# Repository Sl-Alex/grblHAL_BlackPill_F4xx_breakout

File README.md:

# What is it
It's a breakout board for F411 board (black pill) running [grblHAL FW][grblhal_fw]. It is compatible with the default black pill mapping.

## What is tested and confirmed to work

Limits, step/dir outputs and probing are tested and work fine.

> Limits and probing inputs (especially probing) enable a very convenient tool change procedure, when the only thing you have to do is to change the tool and click "cycle start".

Buttons, step enable and spindle enable also work, spindle PWM and auxiliary inputs/outputs are not tested. 

## Pinout

![Pinout][pinout]

The left part of the board is fully isolated from the right part, provided that two isolated power supplies are used.

There is no isolation between the MCU board and the outputs, but this is not a problem taking into account that all these outputs go either to optocouplers or relays.

```NCI``` stands for **N**on-**C**onnected **I**nput, ```NCO``` is an output.

## Remarks

All outputs provide 12V, so be careful connecting step motor drivers without any current limiting circuit.
Some drivers have just one resistor in series with the optocoupler LED, others have a bit more complex constant current circuits, like this:

![Constant current][constant_current]

Most of the drivers without the constant current circuit expect 5V input, so adding a resistor in series with the driver input would be a good solution.
As an alternative, 5V power supply could be used for the output part.

[grblhal_fw]: https://github.com/grblHAL
[pinout]: images/Pinout.png
[constant_current]: images/ConstantCurrent.png

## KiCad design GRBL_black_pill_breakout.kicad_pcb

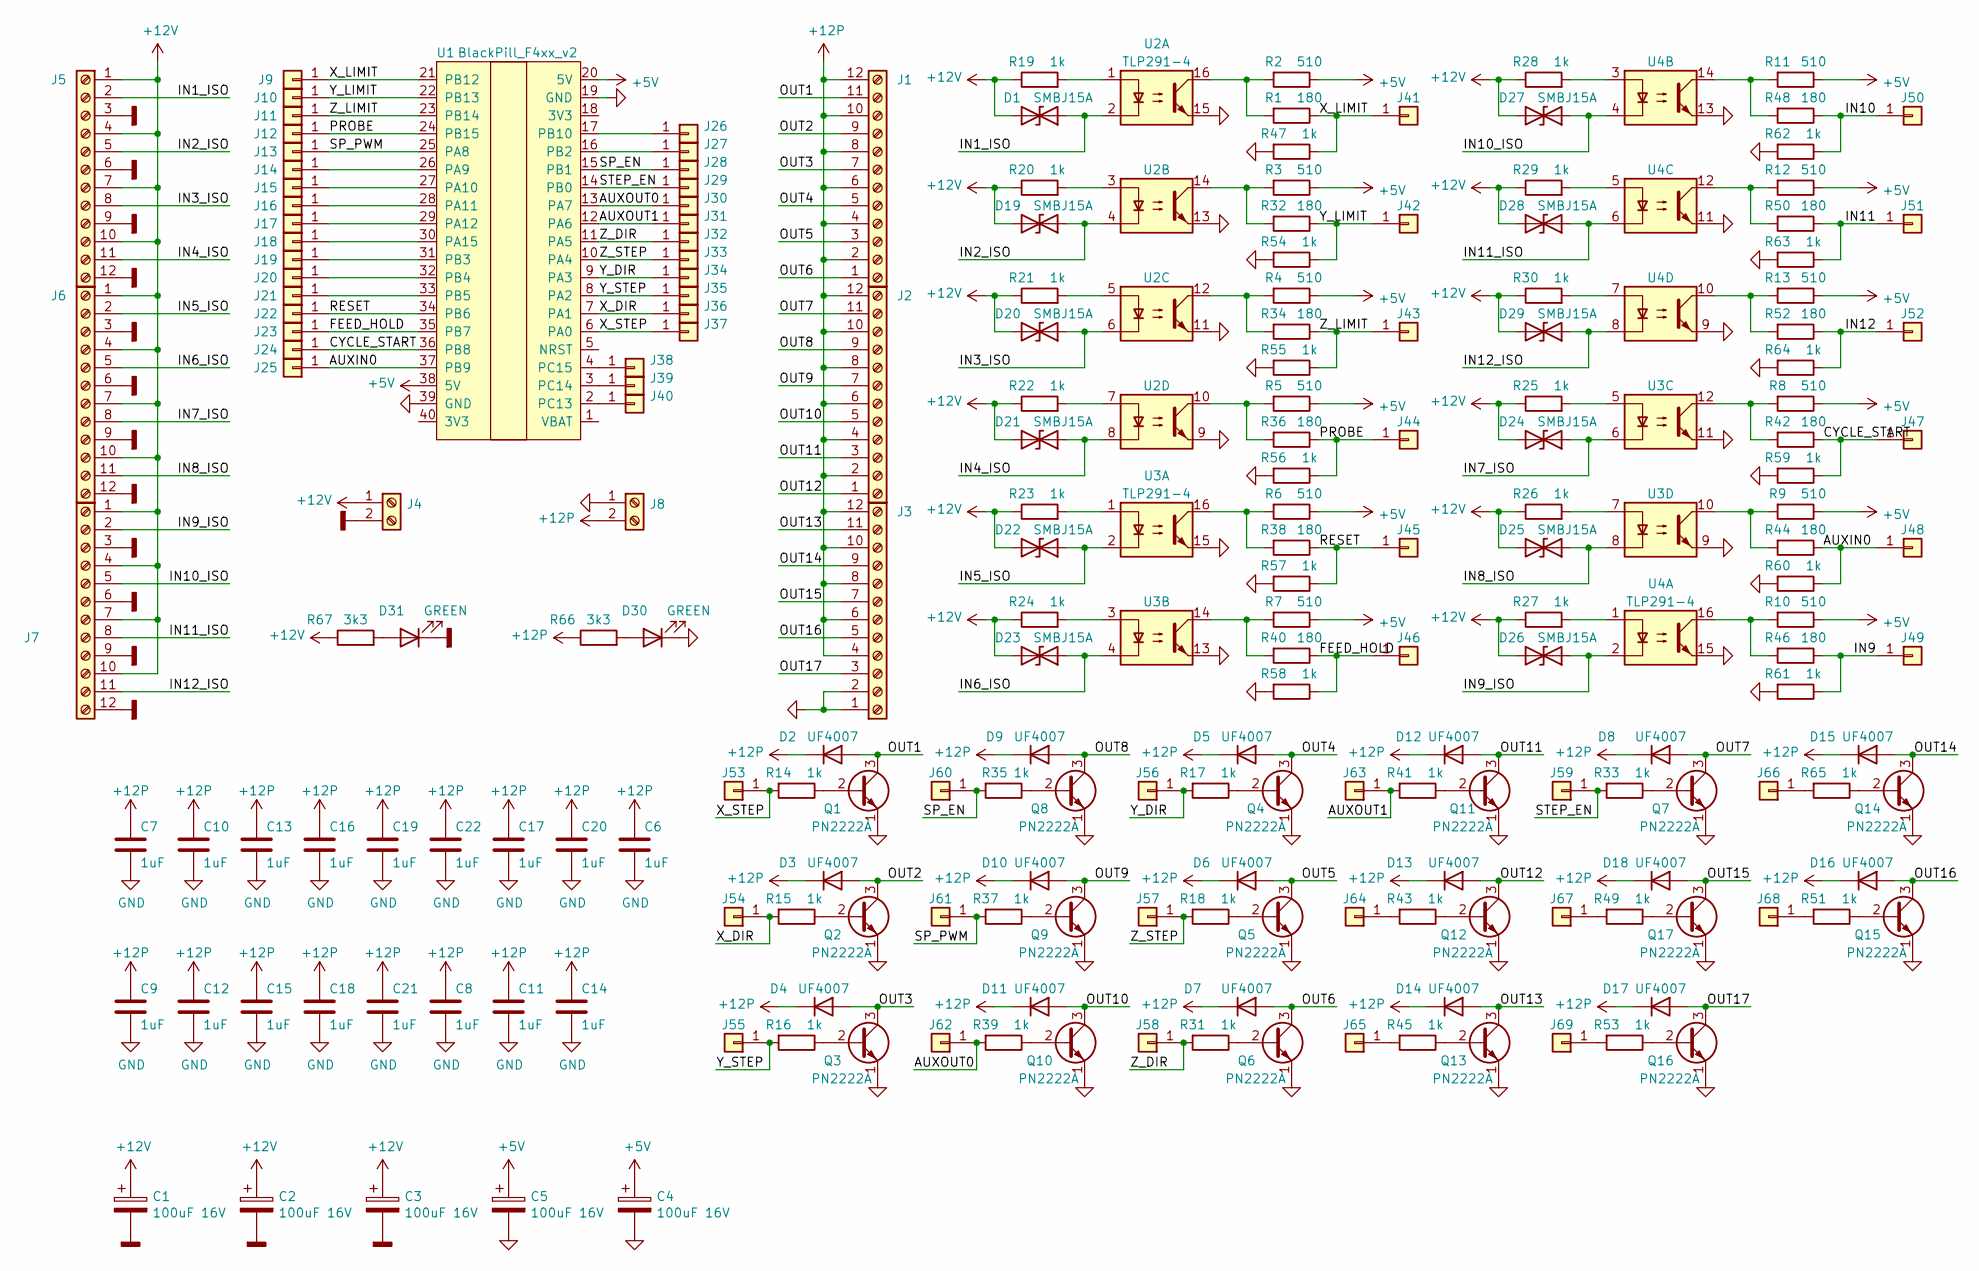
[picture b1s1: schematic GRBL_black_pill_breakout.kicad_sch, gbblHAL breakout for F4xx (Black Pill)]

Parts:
C1, C2, C3, C4, C5: 100uF 16V; CP_Radial_D5.0mm_P2.50mm
C6, C7, C8, C9, C10, C11, C12, C13, C14, C15, C16, C17, C18, C19, C20, C21, C22: 1uF; C_0603_1608Metric
D1, D19, D20, D21, D22, D23, D24, D25, D26, D27, D28, D29: SMBJ15A; D_SMB
D2, D3, D4, D5, D6, D7, D8, D9, D10, D11, D12, D13, D14, D15, D16, D17, D18: UF4007; D_DO-41_SOD81_P2.54mm_Vertical_KathodeUp
D30, D31: GREEN; LED_D3.0mm
J1, J2, J3, J5, J6, J7: Screw_Terminal_01x12; TerminalBlock_Phoenix_MPT-0,5-12-2.54_1x12_P2.54mm_Horizont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
J4, J8: Screw_Terminal_01x02; TerminalBlock_Phoenix_MKDS-1,5-2-5.08_1x02_P5.08mm_Horizont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
J9, J10, J11, J12, J13, J14, J15, J16, J17, J18, J19, J20, J21, J22, J23, J24, J25, J26, J27, J28, J29, J30, J31, J32, J33, J34, J35, J36, J37, J38, J39, J40, J41, J42, J43, J44, J45, J46, J47, J48, J49, J50, J51, J52, J53, J54, J55, J56, J57, J58, J59, J60, J61, J62, J63, J64, J65, J66, J67, J68, J69: Conn_01x01; PinHeader_1x01_P2.54mm_Vertical
Q1, Q2, Q3, Q4, Q5, Q6, Q7, Q8, Q9, Q10, Q11, Q12, Q13, Q14, Q15, Q16, Q17: PN2222A; TO-92_Inline
R1, R32, R34, R36, R38, R40, R42, R44, R46, R48, R50, R52: 180; R_0603_1608Metric
R2, R3, R4, R5, R6, R7, R8, R9, R10, R11, R12, R13: 510; R_0603_1608Metric
R14, R15, R16, R17, R18, R31, R33, R35, R37, R39, R41, R43, R45, R47, R49, R51, R53, R54, R55, R56, R57, R58, R59, R60, R61, R62, R63, R64, R65: 1k; R_0603_1608Metric
R19, R20, R21, R22, R23, R24, R25, R26, R27, R28, R29, R30: 1k; R_Axial_DIN0207_L6.3mm_D2.5mm_P2.54mm_Vertical
R66, R67: 3k3; R_Axial_DIN0207_L6.3mm_D2.5mm_P2.54mm_Vertical
U1: BlackPill_F4xx_v2
U2, U3, U4: TLP291-4; SOP-16_4.4x10.4mm_P1.27mm

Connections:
+5V: C4.1, C5.1, R2.1, R3.1, R4.1, R5.1, R6.1, R7.1, R8.1, R9.1, R10.1, R11.1, R12.1, R13.1, U1.20 (5V), U1.38 (5V)
+12P: C6.1, C7.1, C8.1, C9.1, C10.1, C11.1, C12.1, C13.1, C14.1, C15.1, C16.1, C17.1, C18.1, C19.1, C20.1, C21.1, C22.1, D2.1 (K), D3.1 (K), D4.1 (K), D5.1 (K), D6.1 (K), D7.1 (K), D8.1 (K), D9.1 (K), D10.1 (K), D11.1 (K), D12.1 (K), D13.1 (K), D14.1 (K), D15.1 (K), D16.1 (K), D17.1 (K), D18.1 (K), J1.2, J1.4, J1.6, J1.8, J1.10, J1.12, J2.2, J2.4, J2.6, J2.8, J2.10, J2.12, J3.4, J3.6, J3.8, J3.10, J3.12, J8.2, R66.1
+12V: C1.1, C2.1, C3.1, D1.2 (A2), D19.2 (A2), D20.2 (A2), D21.2 (A2), D22.2 (A2), D23.2 (A2), D24.2 (A2), D25.2 (A2), D26.2 (A2), D27.2 (A2), D28.2 (A2), D29.2 (A2), J4.1, J5.1, J5.4, J5.7, J5.10, J6.1, J6.4, J6.7, J6.10, J7.1, J7.4, J7.7, J7.10, R19.1, R20.1, R21.1, R22.1, R23.1, R24.1, R25.1, R26.1, R27.1, R28.1, R29.1, R30.1, R67.1
/AUXIN0: J25.1, J48.1, R44.1, R60.1, U1.37 (PB9)
/AUXOUT0: J30.1, J62.1, R39.2, U1.13 (PA7)
/AUXOUT1: J31.1, J63.1, R41.2, U1.12 (PA6)
/CYCLE_START: J24.1, J47.1, R42.1, R59.1, U1.36 (PB8)
/FEED_HOLD: J23.1, J46.1, R40.1, R58.1, U1.35 (PB7)
/IN1_ISO: D1.1 (A1), J5.2, U2.2
/IN2_ISO: D19.1 (A1), J5.5, U2.4
/IN3_ISO: D20.1 (A1), J5.8, U2.6
/IN4_ISO: D21.1 (A1), J5.11, U2.8
/IN5_ISO: D22.1 (A1), J6.2, U3.2
/IN6_ISO: D23.1 (A1), J6.5, U3.4
/IN7_ISO: D24.1 (A1), J6.8, U3.6
/IN8_ISO: D25.1 (A1), J6.11, U3.8
/IN9: J49.1, R46.1, R61.1
/IN9_ISO: D26.1 (A1), J7.2, U4.2
/IN10: J50.1, R48.1, R62.1
/IN10_ISO: D27.1 (A1), J7.5, U4.4
/IN11: J51.1, R50.1, R63.1
/IN11_ISO: D28.1 (A1), J7.8, U4.6
/IN12: J52.1, R52.1, R64.1
/IN12_ISO: D29.1 (A1), J7.11, U4.8
/OUT1: D2.2 (A), J1.11, Q1.3 (C)
/OUT2: D3.2 (A), J1.9, Q2.3 (C)
/OUT3: D4.2 (A), J1.7, Q3.3 (C)
/OUT4: D5.2 (A), J1.5, Q4.3 (C)
/OUT5: D6.2 (A), J1.3, Q5.3 (C)
/OUT6: D7.2 (A), J1.1, Q6.3 (C)
/OUT7: D8.2 (A), J2.11, Q7.3 (C)
/OUT8: D9.2 (A), J2.9, Q8.3 (C)
/OUT9: D10.2 (A), J2.7, Q9.3 (C)
/OUT10: D11.2 (A), J2.5, Q10.3 (C)
/OUT11: D12.2 (A), J2.3, Q11.3 (C)
/OUT12: D13.2 (A), J2.1, Q12.3 (C)
/OUT13: D14.2 (A), J3.11, Q13.3 (C)
/OUT14: D15.2 (A), J3.9, Q14.3 (C)
/OUT15: D18.2 (A), J3.7, Q17.3 (C)
/OUT16: D16.2 (A), J3.5, Q15.3 (C)
/OUT17: D17.2 (A), J3.3, Q16.3 (C)
/PROBE: J12.1, J44.1, R36.1, R56.1, U1.24 (PB15)
/RESET: J22.1, J45.1, R38.1, R57.1, U1.34 (PB6)
/SP_EN: J28.1, J60.1, R35.2, U1.15 (PB1)
/SP_PWM: J13.1, J61.1, R37.2, U1.25 (PA8)
/STEP_EN: J29.1, J59.1, R33.2, U1.14 (PB0)
/X_DIR: J36.1, J54.1, R15.2, U1.7 (PA1)
/X_LIMIT: J9.1, J41.1, R1.1, R47.1, U1.21 (PB12)
/X_STEP: J37.1, J53.1, R14.2, U1.6 (PA0)
/Y_DIR: J34.1, J56.1, R17.2, U1.9 (PA3)
/Y_LIMIT: J10.1, J42.1, R32.1, R54.1, U1.22 (PB13)
/Y_STEP: J35.1, J55.1, R16.2, U1.8 (PA2)
/Z_DIR: J32.1, J58.1, R31.2, U1.11 (PA5)
/Z_LIMIT: J11.1, J43.1, R34.1, R55.1, U1.23 (PB14)
/Z_STEP: J33.1, J57.1, R18.2, U1.10 (PA4)
GND: C4.2, C5.2, C6.2, C7.2, C8.2, C9.2, C10.2, C11.2, C12.2, C13.2, C14.2, C15.2, C16.2, C17.2, C18.2, C19.2, C20.2, C21.2, C22.2, D30.1 (K), J3.1, J3.2, J8.1, Q1.1 (E), Q2.1 (E), Q3.1 (E), Q4.1 (E), Q5.1 (E), Q6.1 (E), Q7.1 (E), Q8.1 (E), Q9.1 (E), Q10.1 (E), Q11.1 (E), Q12.1 (E), Q13.1 (E), Q14.1 (E), Q15.1 (E), Q16.1 (E), Q17.1 (E), R47.2, R54.2, R55.2, R56.2, R57.2, R58.2, R59.2, R60.2, R61.2, R62.2, R63.2, R64.2, U1.19 (GND), U1.39 (GND), U2.9, U2.11, U2.13, U2.15, U3.9, U3.11, U3.13, U3.15, U4.9, U4.11, U4.13, U4.15
GNDD: C1.2, C2.2, C3.2, D31.1 (K), J4.2, J5.3, J5.6, J5.9, J5.12, J6.3, J6.6, J6.9, J6.12, J7.3, J7.6, J7.9, J7.12
unnamed: D30.2 (A), R66.2
unnamed: D31.2 (A), R67.2
unnamed: J14.1, U1.26 (PA9)
unnamed: J15.1, U1.27 (PA10)
unnamed: J16.1, U1.28 (PA11)
unnamed: J17.1, U1.29 (PA12)
unnamed: J18.1, U1.30 (PA15)
unnamed: J19.1, U1.31 (PB3)
unnamed: J20.1, U1.32 (PB4)
unnamed: J21.1, U1.33 (PB5)
unnamed: J26.1, U1.17 (PB10)
unnamed: J27.1, U1.16 (PB2)
unnamed: J38.1, U1.4 (PC15)
unnamed: J39.1, U1.3 (PC14)
unnamed: J40.1, U1.2 (PC13)
unnamed: J64.1, R43.2
unnamed: J65.1, R45.2
unnamed: J66.1, R65.2
unnamed: J67.1, R49.2
unnamed: J68.1, R51.2
unnamed: J69.1, R53.2
unnamed: Q1.2 (B), R14.1
unnamed: Q2.2 (B), R15.1
unnamed: Q3.2 (B), R16.1
unnamed: Q4.2 (B), R17.1
unnamed: Q5.2 (B), R18.1
unnamed: Q6.2 (B), R31.1
unnamed: Q7.2 (B), R33.1
unnamed: Q8.2 (B), R35.1
unnamed: Q9.2 (B), R37.1
unnamed: Q10.2 (B), R39.1
unnamed: Q11.2 (B), R41.1
unnamed: Q12.2 (B), R43.1
unnamed: Q13.2 (B), R45.1
unnamed: Q14.2 (B), R65.1
unnamed: Q15.2 (B), R51.1
unnamed: Q16.2 (B), R53.1
unnamed: Q17.2 (B), R49.1
unnamed: R1.2, R2.2, U2.16
unnamed: R3.2, R32.2, U2.14
unnamed: R10.2, R46.2, U4.16
unnamed: R11.2, R48.2, U4.14
unnamed: R12.2, R50.2, U4.12
unnamed: R13.2, R52.2, U4.10
unnamed: R19.2, U2.1
unnamed: R20.2, U2.3
unnamed: R21.2, U2.5
unnamed: R22.2, U2.7
unnamed: R23.2, U3.1
unnamed: R24.2, U3.3
unnamed: R25.2, U3.5
unnamed: R26.2, U3.7
unnamed: R27.2, U4.1
unnamed: R28.2, U4.3
unnamed: R29.2, U4.5
unnamed: R30.2, U4.7
unnamed: R4.2, R34.2, U2.12
unnamed: R5.2, R36.2, U2.10
unnamed: R6.2, R38.2, U3.16
unnamed: R7.2, R40.2, U3.14
unnamed: R8.2, R42.2, U3.12
unnamed: R9.2, R44.2, U3.10

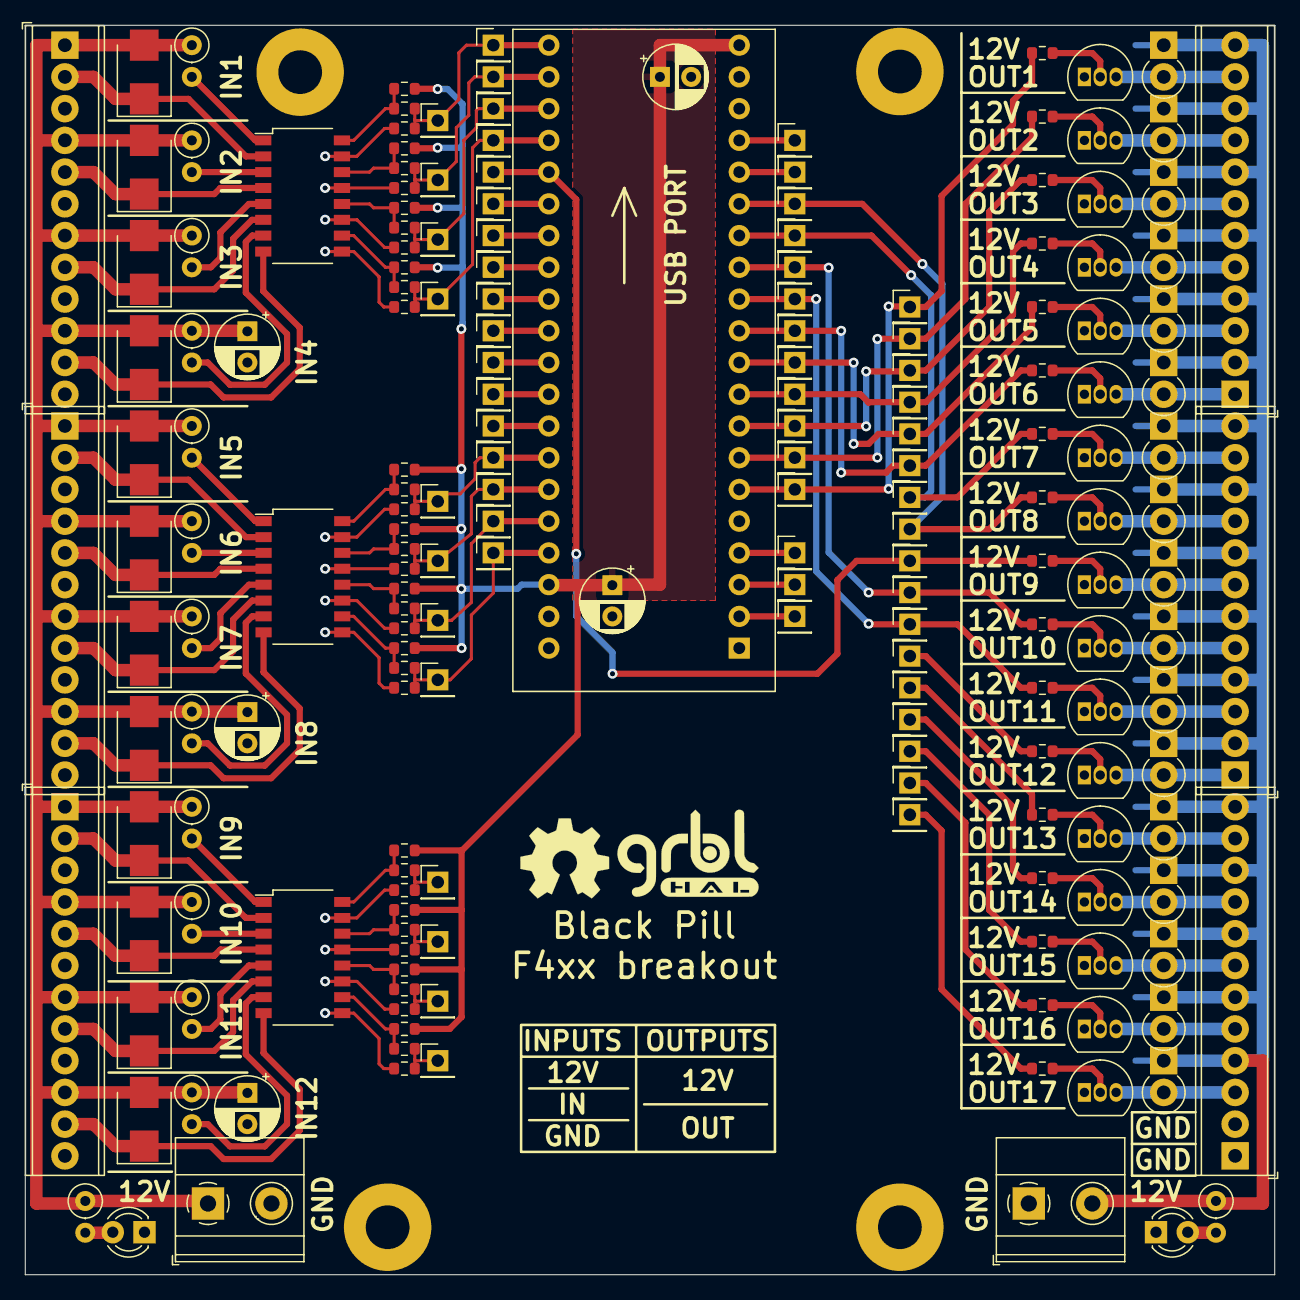
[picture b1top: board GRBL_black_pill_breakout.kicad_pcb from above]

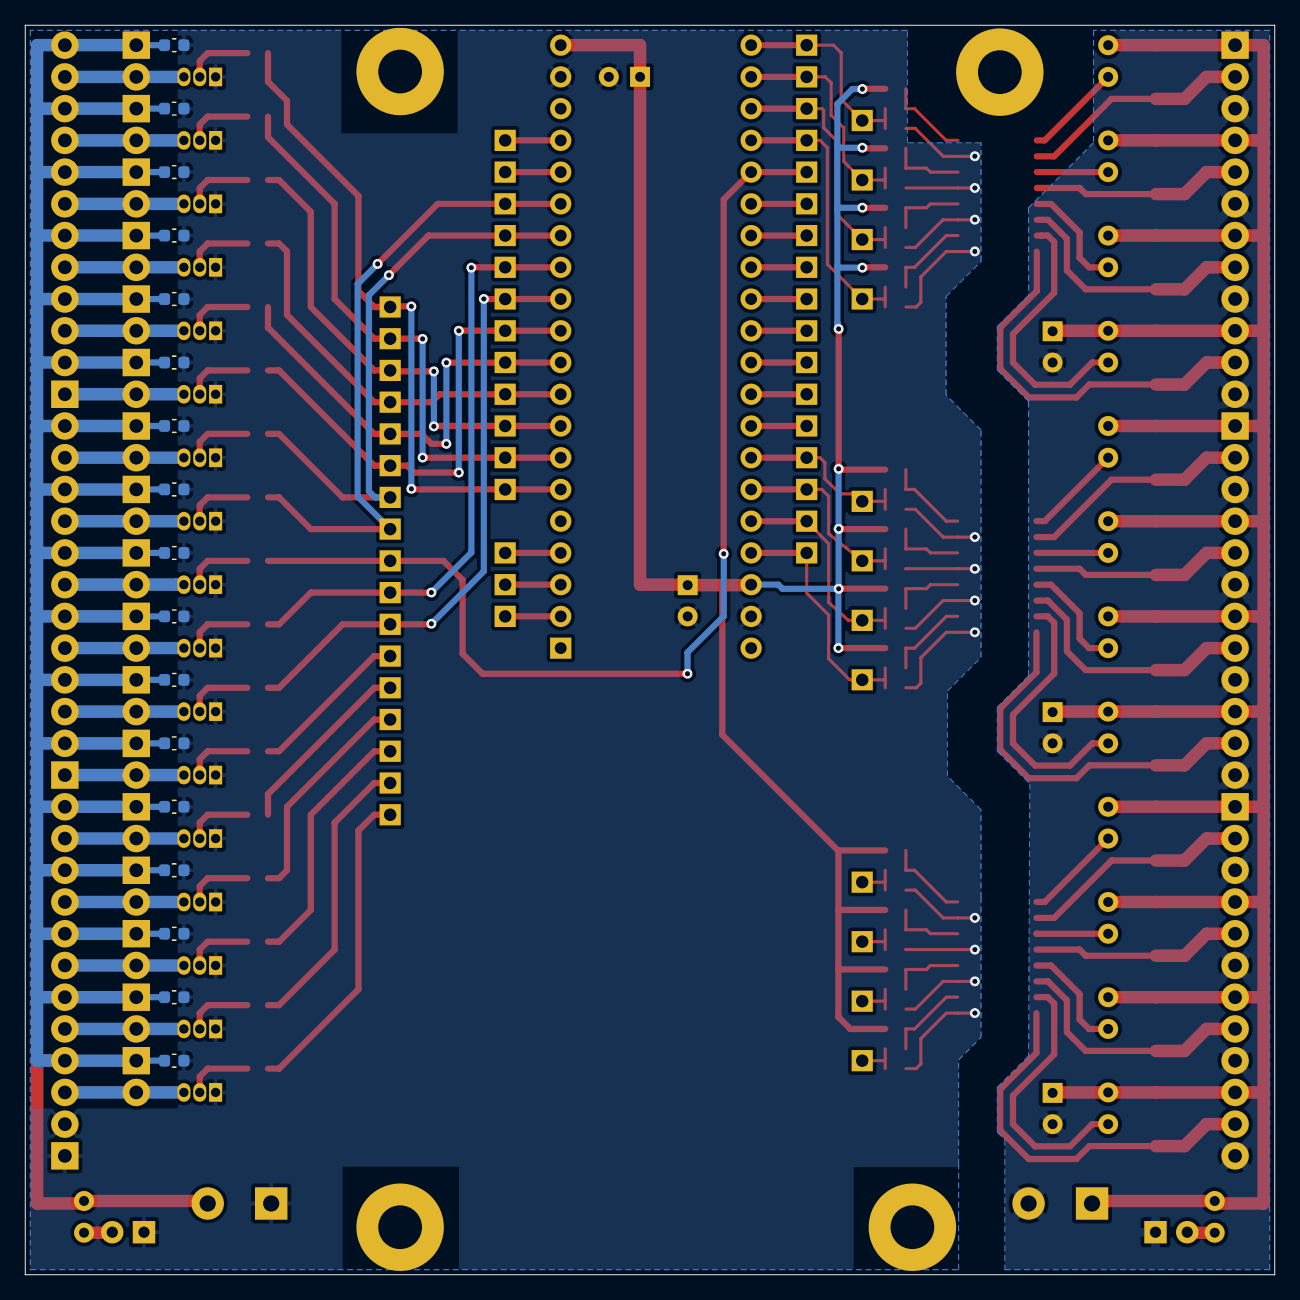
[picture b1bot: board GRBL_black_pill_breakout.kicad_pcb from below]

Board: 2 copper layers, 100.0 x 100.0 mm, 210 parts (17 on the bottom side), 119 nets.

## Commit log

2021-04-17 First prototype
2021-04-21 Flip 12V connectors, update values
2022-06-14 Update the board according to the official GrblHAL pinout for black pill
2022-06-15 Extend README
